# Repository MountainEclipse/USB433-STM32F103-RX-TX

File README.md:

# USB433 - Sniff and Transmit

USB-connected, STM32F103-based 433.92MHz module with asynchronous RX sniffing for OOK protocol

<hr>

*Github Repo: <a href="https://github.com/MountainEclipse/USB433-STM32F103-RX-TX" target="_blank">USB433</a> by <a href="https://github.com/MountainEclipse" target="_blank">MountainEclipse (TimeHack)</a>*

*Assembly Instructable: <a href="https://www.instructables.com/USB433-Sniff-Transmit-OOK-43392-MHz/" target="_blank">USB433 - Sniff & Transmit OOK 433.92 MHz</a>*

<hr>

This project allows you to passively sniff On-Off-Keyed (OOK) signals in the environment - up to 64 bits in length - and transmit OOK messages via a USB-connected radio module. Originally designed to operate 433.92 MHz wireless outlet switches, this module can also receive weather station data and mimic other 433 MHz codes.

Designed to operate on a custom circuit board, this project should equally work with the hobby-friendly BluePill STM32F103 board with jumper wires to OOK RX/TX modules. All design and firmware files are provided as is, for personal hobbyist use under Creative Commons 4.0 Attribution, Non-Commercial (CC BY-NC) international license.

The following is a list of everything you need to make this project:
<ul>
  Hardware:

<li>STM32F103 Microcontroller (the STM32 Blue Pill can work; just pay attention to pinouts)</li>
<li>433 MHz OOK Receiver and Transmitter (I used SRX882 and STX882)</li>
<li>Optional: 3D Printer for printing the enclosure</li>
<li>Optional: LED's for user feedback</li>
<li>4x M3x12 hex socket screws</li>
<li>4x M3 hex nuts</li>
</ul>
<ul>
Software:
<li>KiCAD 6.0 (If you're modifying the PCB or generating the DRL files for PCB fabrication)</li>
<li>STM32CubeIDE (for flashing the STM32 with ease)</li>
<li>Optional: Hercules Setup Utility (for testing serial commands)</li>
</ul>

<hr>
For instructions on assembly, flashing, and testing, please visit the project Instructable <a href="https://www.instructables.com/USB433-Sniff-Transmit-OOK-43392-MHz/" target="_blank">here</a>

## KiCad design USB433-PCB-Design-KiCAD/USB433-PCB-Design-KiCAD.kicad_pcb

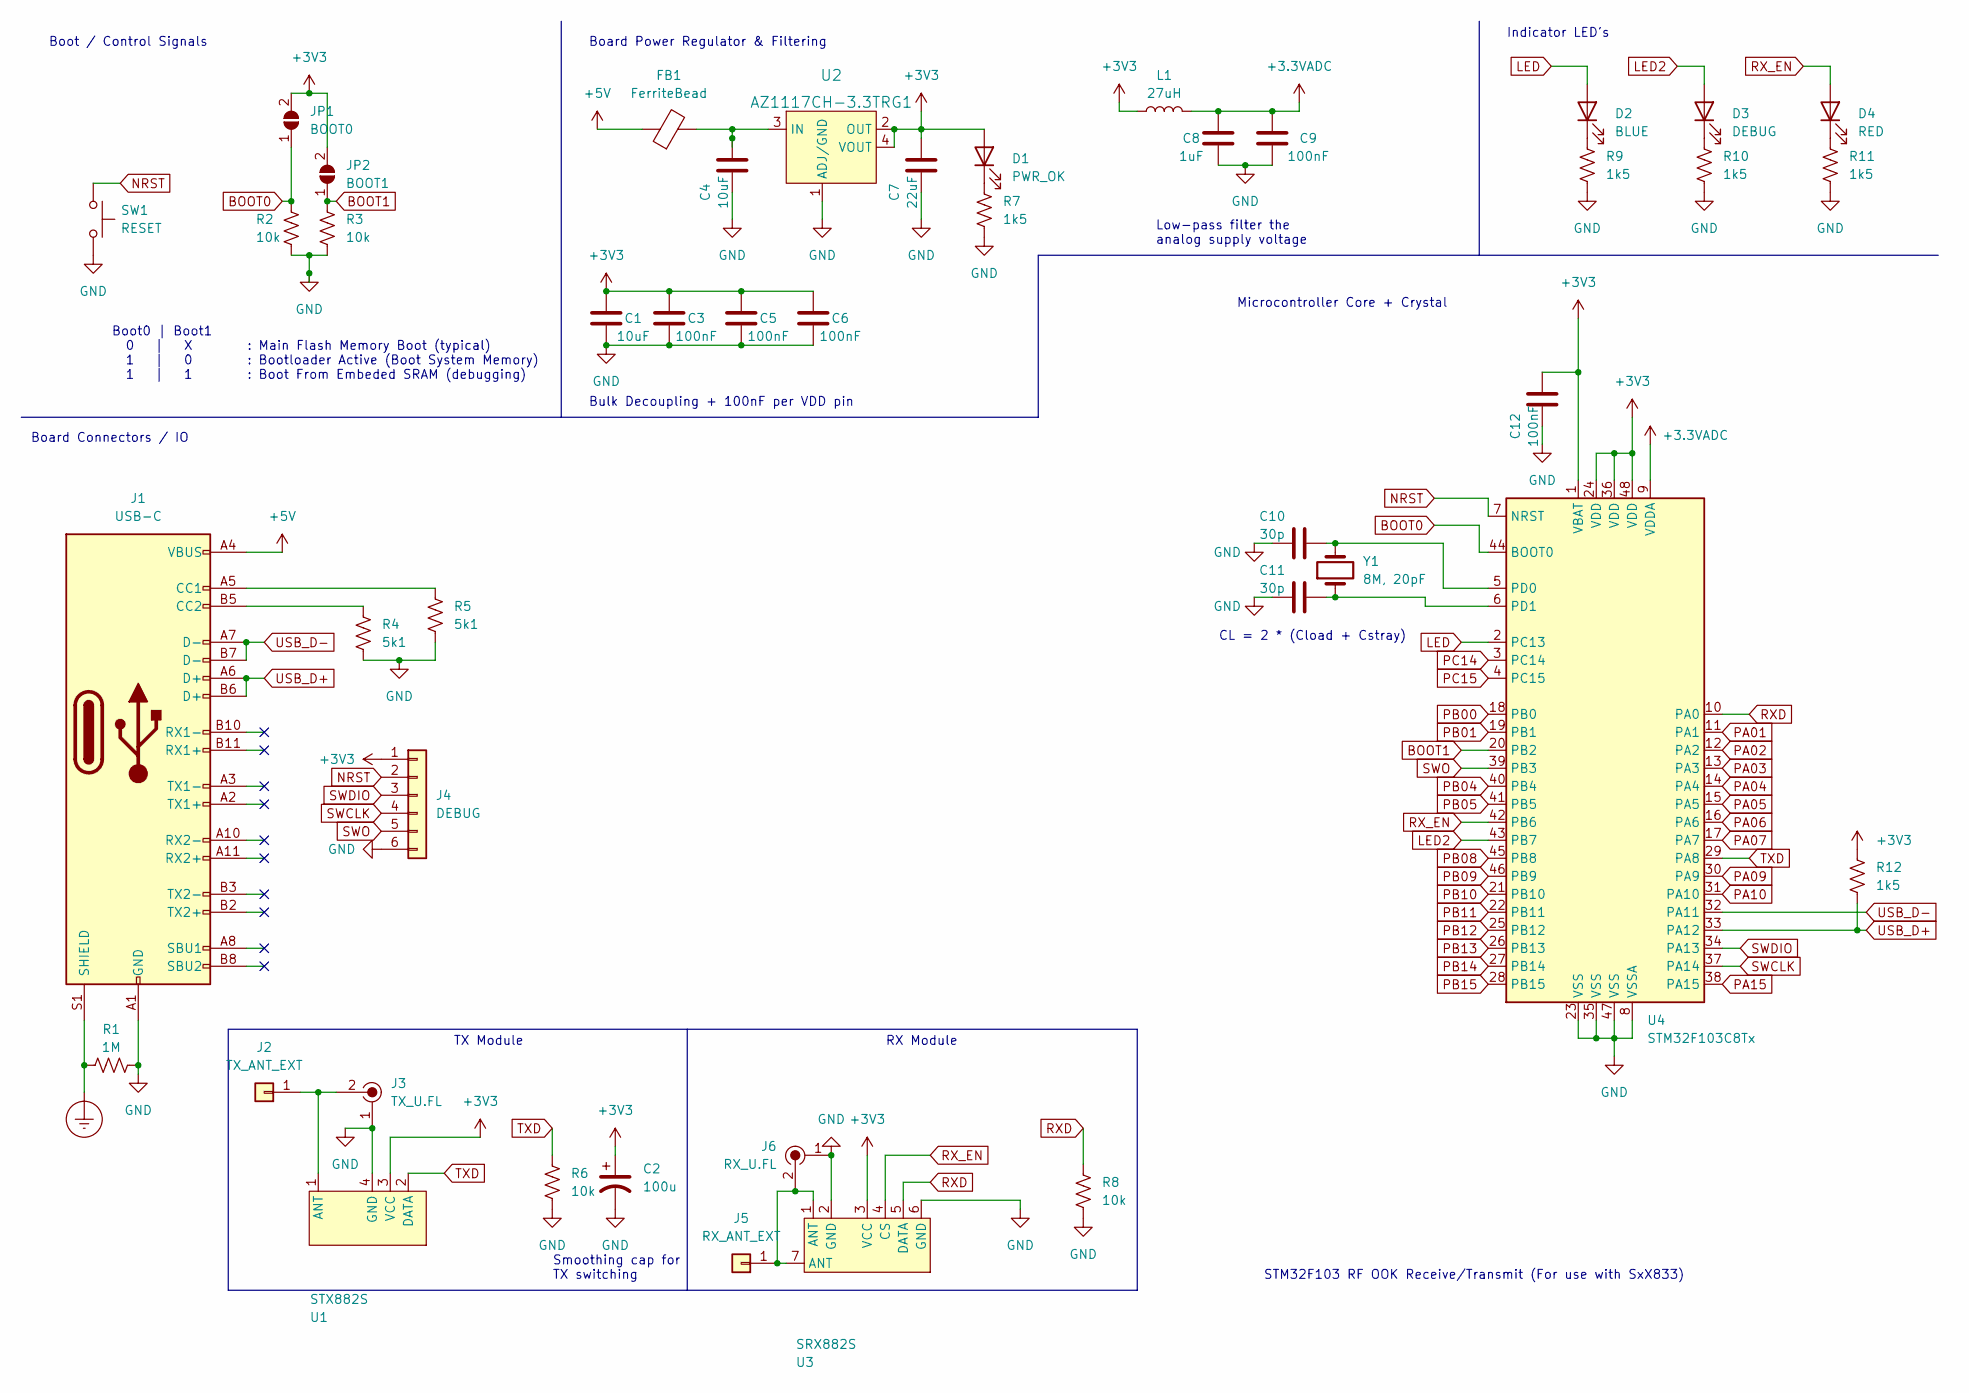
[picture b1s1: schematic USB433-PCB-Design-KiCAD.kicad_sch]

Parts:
C1, C4: 10uF; C_0805_2012Metric
C2: 100u; C_1206_3216Metric_Pad1.33x1.80mm_HandSolder
C3, C5, C6, C9, C12: 100nF; C_0402_1005Metric
C7: 22uF; C_1206_3216Metric
C8: 1uF; C_0603_1608Metric
C10, C11: 30p; C_0402_1005Metric
D1: PWR_OK; LED_0805_2012Metric
D2: BLUE; LED_0805_2012Metric
D3: DEBUG; LED_0805_2012Metric
D4: RED; LED_0805_2012Metric
FB1: FerriteBead; R_0805_2012Metric
J1: USB-C; USB_C_Receptacle_G-Switch_GT-USB-7010ASV
J2: TX_ANT_EXT; PinHeader_1x01_P2.54mm_Vertical
J3: TX_U.FL; Coax_Conn_U.FL; MPN U.FL-R-SMT(10); Digi-Key_PN H9161CT-ND
J4: DEBUG; PinHeader_1x06_P2.54mm_Vertical
J5: RX_ANT_EXT; PinHeader_1x01_P2.54mm_Vertical
J6: RX_U.FL; Coax_Conn_U.FL; MPN U.FL-R-SMT(10); Digi-Key_PN H9161CT-ND
JP1: BOOT0; SolderJumper-2_P1.3mm_Open_RoundedPad1.0x1.5mm
JP2: BOOT1; SolderJumper-2_P1.3mm_Open_RoundedPad1.0x1.5mm
L1: 27uH; L_0805_2012Metric
R1: 1M; R_0805_2012Metric
R2, R3, R6, R8: 10k; R_0805_2012Metric
R4, R5: 5k1; R_0805_2012Metric
R7, R9, R10, R11, R12: 1k5; R_0805_2012Metric
SW1: RESET; SW_Push_1P1T_W6.8mm_H4.6mm
U1: STX882S; STX882-THT
U2: AZ1117CH-3.3TRG1; SOT-223; MPN AZ1117CH-3.3TRG1; Digi-Key_PN AZ1117CH-3.3TRG1DICT-ND
U3: SRX882S; SRX882-THT
U4: STM32F103C8Tx; LQFP-48_7x7mm_P0.5mm
Y1: 8M, 20pF; Crystal_SMD_5032-2Pin_5.0x3.2mm

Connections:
+3.3VADC: C8.2, C9.2, L1.2, U4.9 (VDDA)
+3V3: C1.2, C2.1, C3.2, C5.2, C6.2, C7.2, C12.2, D1.2 (A), J4.1, JP1.2 (B), JP2.2 (B), L1.1, R12.2, U1.3 (VCC), U2.2 (OUT), U2.4 (VOUT), U3.3 (VCC), U4.1 (VBAT), U4.24 (VDD), U4.36 (VDD), U4.48 (VDD)
+5V: FB1.1, J1.A4 (VBUS), J1.A9 (VBUS), J1.B4 (VBUS), J1.B9 (VBUS)
BOOT0: JP1.1 (A), R2.2, U4.44 (BOOT0)
BOOT1: JP2.1 (A), R3.1, U4.20 (PB2)
Earth_Protective: J1.S1 (SHIELD), R1.1; also elsewhere on the board
GND: C1.1, C2.2, C3.1, C4.1, C5.1, C6.1, C7.1, C8.1, C9.1, C10.1, C11.1, C12.1, J1.A1 (GND), J1.A12 (GND), J1.B1 (GND), J1.B12 (GND), J3.1, J4.6, J6.1, R1.2, R2.1, R3.2, R4.2, R5.2, R6.2, R7.2, R8.2, R9.2, R10.2, R11.2, SW1.2, U1.4 (GND), U2.1 (ADJ/GND), U3.2 (GND), U3.6 (GND), U4.8 (VSSA), U4.23 (VSS), U4.35 (VSS), U4.47 (VSS)
LED: D2.2 (A), U4.2 (PC13)
LED2: D3.2 (A), U4.43 (PB7)
NRST: J4.2, SW1.1, U4.7 (NRST)
unnamed: C4.2, FB1.2, U2.3 (IN)
unnamed: C10.2, U4.5 (PD0), Y1.2
unnamed: C11.2, U4.6 (PD1), Y1.1
unnamed: D1.1 (K), R7.1
unnamed: D2.1 (K), R9.1
unnamed: D3.1 (K), R10.1
unnamed: D4.1 (K), R11.1
unnamed: J1.A5 (CC1), R5.1
unnamed: J1.B5 (CC2), R4.1
unnamed: J2.1, J3.2, U1.1 (ANT)
unnamed: J5.1, J6.2, U3.1 (ANT), U3.7 (ANT)
PA01: U4.11 (PA1)
PA02: U4.12 (PA2)
PA03: U4.13 (PA3)
PA04: U4.14 (PA4)
PA05: U4.15 (PA5)
PA06: U4.16 (PA6)
PA07: U4.17 (PA7)
PA09: U4.30 (PA9)
PA10: U4.31 (PA10)
PA15: U4.38 (PA15)
PB00: U4.18 (PB0)
PB01: U4.19 (PB1)
PB04: U4.40 (PB4)
PB05: U4.41 (PB5)
PB08: U4.45 (PB8)
PB09: U4.46 (PB9)
PB10: U4.21 (PB10)
PB11: U4.22 (PB11)
PB12: U4.25 (PB12)
PB13: U4.26 (PB13)
PB14: U4.27 (PB14)
PB15: U4.28 (PB15)
PC14: U4.3 (PC14)
PC15: U4.4 (PC15)
RXD: R8.1, U3.5 (DATA), U4.10 (PA0)
RX_EN: D4.2 (A), U3.4 (CS), U4.42 (PB6)
SWCLK: J4.4, U4.37 (PA14)
SWDIO: J4.3, U4.34 (PA13)
SWO: J4.5, U4.39 (PB3)
TXD: R6.1, U1.2 (DATA), U4.29 (PA8)
USB_D+: J1.A6 (D+), J1.B6 (D+), R12.1, U4.33 (PA12)
USB_D-: J1.A7 (D-), J1.B7 (D-), U4.32 (PA11)

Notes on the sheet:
STM32F103 RF OOK Receive/Transmit (For use with SxX833)
Boot0 | Boot1 0 | X : Main Flash Memory Boot (typical) 1 | 0 : Bootloader Active (Boot System Memory) 1 | 1 : Boot From Embeded SRAM (debugging)
TX Module
Indicator LED's
Board Connectors / IO
Boot / Control Signals
RX Module
Smoothing cap for TX switching
CL = 2 * (Cload + Cstray)
Board Power Regulator & Filtering
Bulk Decoupling + 100nF per VDD pin
Microcontroller Core + Crystal
Low-pass filter the analog supply voltage

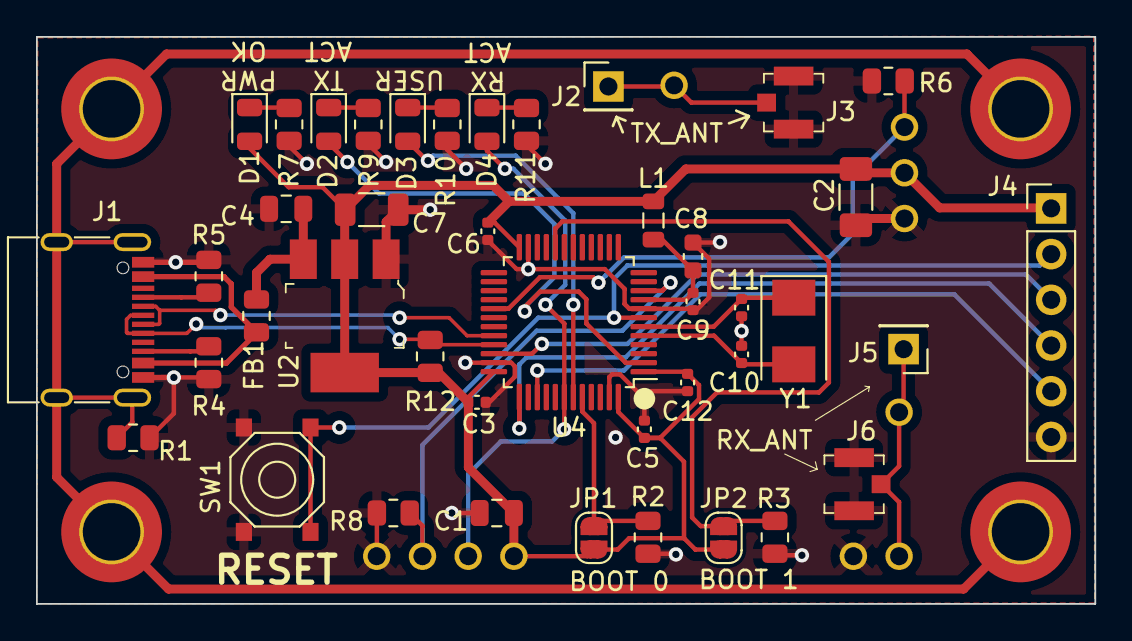
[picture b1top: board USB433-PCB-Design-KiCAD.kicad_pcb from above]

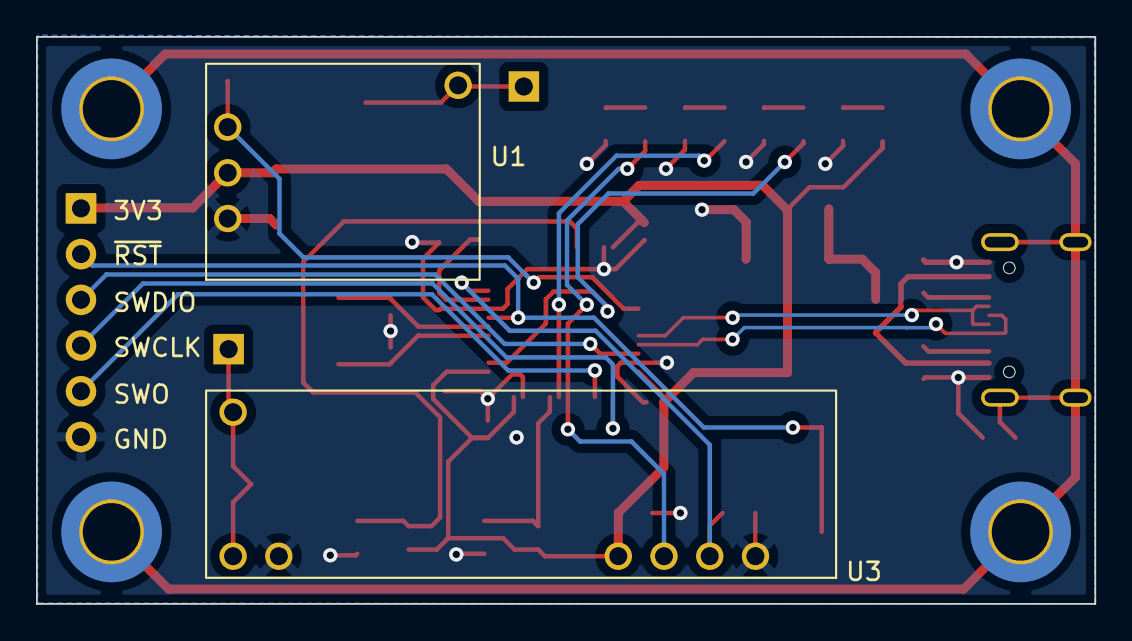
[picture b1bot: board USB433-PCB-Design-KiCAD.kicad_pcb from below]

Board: 2 copper layers, 58.8 x 31.5 mm, 48 parts (2 on the bottom side), 29 nets.

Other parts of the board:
M3, M3#2, M3#3, M3#4: Mount; MountingHole_3.2mm_M3_DIN965_Pad_TopBottom

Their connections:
Earth_Protective: M3.1, M3#2.1, M3#3.1, M3#4.1; also elsewhere on the board

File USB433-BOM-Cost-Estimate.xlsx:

Source: | \\DS1821plus\documents\03-Hobbies & Projects\15-Business Products\433MHz-SRX882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
Date: | 45806.363622685189
Tool: | Eeschema (6.0.11)
Generator: | C:\Program Files\KiCad\6.0\bin\scripting\plugins/bom_csv_grouped_by_value_with_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
Component Count: | 44
Ref | Qnty | Value | Cmp name | Footprint | Description | Price | Cost | Vendor | Link
C1, C4, | 2 | 10uF | C | Capacitor_SMD:C_0805_2012Metric | Unpolarized capacitor | 1.04E-2 | 2.0799999999999999E-2 | LCSC | https://www.lcsc.com/product-detail/Multilayer-Ceramic-Capac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
C2, | 1 | 100u | C_Polarized_US | Capacitor_SMD:C_1206_3216Metric_Pad1.33x1.80mm_HandSolder | Polarized capacitor, US symbol | 0.1802 | 0.1802 | LCSC | https://www.lcsc.com/product-detail/Multilayer-Ceramic-Capac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
C3, C5, C6, C9, C12, | 5 | 100nF | C | Capacitor_SMD:C_0402_1005Metric | Unpolarized capacitor | 1.6999999999999999E-3 | 8.4999999999999989E-3 | LCSC | https://www.lcsc.com/product-detail/Multilayer-Ceramic-Capac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
C7, | 1 | 22uF | C | Capacitor_SMD:C_1206_3216Metric | Unpolarized capacitor | 2.4799999999999999E-2 | 2.4799999999999999E-2 | LCSC | https://www.lcsc.com/product-detail/Multilayer-Ceramic-Capac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
C8, | 1 | 1uF | C | Capacitor_SMD:C_0603_1608Metric | Unpolarized capacitor | 5.1999999999999998E-3 | 5.1999999999999998E-3 | LCSC | https://www.lcsc.com/product-detail/Multilayer-Ceramic-Capac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
C10, C11, | 2 | 30p | C | Capacitor_SMD:C_0402_1005Metric | Unpolarized capacitor | 1.1999999999999999E-3 | 2.3999999999999998E-3 | LCSC | https://www.lcsc.com/product-detail/Multilayer-Ceramic-Capac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
D1, D3, D4, | 3 | PWR_OK, DEBUG, RED | LED | LED_SMD:LED_0805_2012Metric | Light emitting diode | 5.7000000000000002E-3 | 1.7100000000000001E-2 | LCSC | https://www.lcsc.com/product-detail/LED-Indication-Discrete_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
D2, | 1 | BLUE | LED | LED_SMD:LED_0805_2012Metric | Light emitting diode | 2.3900000000000001E-2 | 2.3900000000000001E-2 | LCSC | https://www.lcsc.com/product-detail/LED-Indication-Discrete_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
FB1, | 1 | FerriteBead | FerriteBead | Resistor_SMD:R_0805_2012Metric | Ferrite bead | 4.1000000000000003E-3 | 4.1000000000000003E-3 | LCSC | https://www.lcsc.com/product-detail/Ferrite-Beads_MetalLions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
J1, | 1 | USB-C | USB_C_Receptacle | Connector_USB:USB_C_Receptacle_G-Switch_GT-USB-7010ASV | USB Full-Featured Type-C Receptacle connector | 7.6100000000000001E-2 | 7.6100000000000001E-2 | LCSC | https://www.lcsc.com/product-detail/USB-Connectors_G-Switch-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
J2, J5 | 2 | TX_ANT_EXT, RX_ANT_EXT | Conn_01x01 | Connector_PinHeader_2.54mm:PinHeader_1x01_P2.54mm_Vertical | Generic connector, single row, 01x01, script generated (kicad-library-utils/sch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 |  | 0
J3, J6 | 2 | TX_U.FL, RX_U.FL | U_FL-R-SMT_10_ | digikey-footprints:Coax_Conn_U.FL | CONN U.FL RCPT STR 50 OHM SMD | 3.3099999999999997E-2 | 6.6199999999999995E-2 | LCSC | https://www.lcsc.com/product-detail/Coaxial-Connectors-RF_BA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
J4, | 1 | DEBUG | Conn_01x06 | Connector_PinHeader_2.54mm:PinHeader_1x06_P2.54mm_Vertical | Generic connector, single row, 01x06, script generated (kicad-library-utils/sch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 |  | 0
JP1, | 1 | BOOT0 | SolderJumper_2_Open | Jumper:SolderJumper-2_P1.3mm_Open_RoundedPad1.0x1.5mm | Solder Jumper, 2-pole, open |  | 0
JP2, | 1 | BOOT1 | SolderJumper_2_Open | Jumper:SolderJumper-2_P1.3mm_Open_RoundedPad1.0x1.5mm | Solder Jumper, 2-pole, open |  | 0
L1, | 1 | 27uH | L | Inductor_SMD:L_0805_2012Metric | Inductor | 2.3300000000000001E-2 | 2.3300000000000001E-2 | LCSC | https://www.lcsc.com/product-detail/Inductors-SMD_XR-XRCM201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
R1, | 1 | 1M | R_US | Resistor_SMD:R_0805_2012Metric | Resistor, US symbol | 7.7000000000000002E-3 | 7.7000000000000002E-3 | LCSC | https://www.lcsc.com/product-detail/Chip-Resistor-Surface-Mo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
R2, R3, R6, R8, | 4 | 10k | R_US | Resistor_SMD:R_0805_2012Metric | Resistor, US symbol | 9.7999999999999997E-3 | 3.9199999999999999E-2 | LCSC | https://www.lcsc.com/product-detail/Chip-Resistor-Surface-Mo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
R4, R5, | 2 | 5k1 | R_US | Resistor_SMD:R_0805_2012Metric | Resistor, US symbol | 7.7999999999999996E-3 | 1.5599999999999999E-2 | LCSC | https://www.lcsc.com/product-detail/Chip-Resistor-Surface-Mo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
R7, R9, R10, R11, R12, | 5 | 1k5 | R_US | Resistor_SMD:R_0805_2012Metric | Resistor, US symbol | 1.0200000000000001E-2 | 5.1000000000000004E-2 | LCSC | https://www.lcsc.com/product-detail/Chip-Resistor-Surface-Mo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
SW1, | 1 | RESET | SW_Push | User_Custom:SW_Push_1P1T_W6.8mm_H4.6mm | Push button switch, generic, two pins | 1.2200000000000001E-2 | 1.2200000000000001E-2 | LCSC | https://www.lcsc.com/product-detail/Tactile-Switches_BZCN-TS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
U1, | 1 | STX882S | STX882S | User_Custom:STX882-THT |  | 1.87375 | 1.87375 | Amazon | https://www.amazon.com/AITIAO-Wireless-Control-Transmitter-R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
U2, | 1 | AZ1117CH-3.3TRG1 | AZ1117CH-3_3TRG1 | digikey-footprints:SOT-223 | IC REG LINEAR 3.3V 800MA SOT223 | 7.22E-2 | 7.22E-2 | LCSC | https://www.lcsc.com/product-detail/Linear-Voltage-Regulator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
U3, | 1 | SRX882S | SRX882S | User_Custom:SRX882-THT |  | 1.87375 | 1.87375 | Amazon | https://www.amazon.com/AITIAO-Wireless-Control-Transmitter-R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
U4, | 1 | STM32F103C8Tx | STM32F103C8Tx | Package_QFP:LQFP-48_7x7mm_P0.5mm | ARM Cortex-M3 MCU, 64KB flash, 20KB RAM, 72MHz, 2-3.6V, 37 GPIO, LQFP-48 | 1.7009000000000001 | 1.7009000000000001 | ARROW | https://www.arrow.com/en/products/stm32f103c8t6/stmicroelectronics
Y1, | 1 | 8M, 20pF | Crystal | Crystal:Crystal_SMD_5032-2Pin_5.0x3.2mm | Two pin crystal | 0.2056 | 0.2056 | LCSC | https://www.lcsc.com/product-detail/Crystals_Yangxing-Tech-X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
 |  |  |  |  |  | Components | 6.3044999999999991
 |  |  |  |  |  | Board Fab | 4.7666666666666666
 |  |  |  |  |  | Stencil | 9.69 | 29.07
 |  |  |  |  |  |  | 20.761166666666668 |  |  | PCB Fab | Round | Bulk Cost | Qty
 |  |  |  |  |  |  |  |  |  |  | 1 | 14.3 | 3
 |  |  |  |  |  |  |  |  |  |  | 2
 |  |  |  |  |  |  |  |  |  |  | 3
 |  |  |  |  |  |  |  |  |  |  | 4
 |  |  |  |  |  |  |  |  |  |  | 5
 |  |  |  |  |  |  |  |  |  |  | 6
 |  |  |  |  |  |  |  |  |  |  | 7
 |  |  |  |  |  |  |  |  |  |  | 8
 |  |  |  |  |  |  |  |  |  |  | 9

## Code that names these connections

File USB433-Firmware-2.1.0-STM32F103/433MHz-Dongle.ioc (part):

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Mcu.Name=STM32F103C(8-B)Tx
Mcu.Package=LQFP48
Mcu.UserName=STM32F103C8Tx
PA0-WKUP.Signal=S_TIM2_CH1_ETR
PA11.Mode=Device
PA11.Signal=USB_DM
PA12.Mode=Device
PA12.Signal=USB_DP
PA13.Mode=Trace_Asynchronous_SW
PA13.Signal=SYS_JTMS-SWDIO
PA14.Mode=Trace_Asynchronous_SW
PA14.Signal=SYS_JTCK-SWCLK
PA8.Signal=S_TIM1_CH1
PB3.Mode=Trace_Asynchronous_SW
PB3.Signal=SYS_JTDO-TRACESWO
PB6.GPIOParameters=GPIO_Label
PB6.GPIO_Label=RX_EN
PB6.Signal=GPIO_Output
PB7.GPIOParameters=GPIO_Label
PB7.GPIO_Label=TX_ACT
PB7.Signal=GPIO_Output
PC13-TAMPER-RTC.GPIOParameters=GPIO_Label
PC13-TAMPER-RTC.GPIO_Label=USB_ACT
PC13-TAMPER-RTC.Signal=GPIO_Output
PD0-OSC_IN.Mode=HSE-External-Oscillator
PD0-OSC_IN.Signal=RCC_OSC_IN
PD1-OSC_OUT.Mode=HSE-External-Oscillator
PD1-OSC_OUT.Signal=RCC_OSC_OUT
RCC.SYSCLKFreq_VALUE=72000000
RCC.SYSCLKSource=RCC_SYSCLKSOURCE_PLLCLK
board=custom

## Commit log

2025-09-28 Instructable Published
2025-09-28 Updated Cost Estimate Sheet
